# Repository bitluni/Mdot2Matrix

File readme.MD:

# M.2 LED Matrix

## Goal

This project is a showcase and starting point for M.2 PCIe hardware. The interface chip CH382 was used to inteface between the first PCIe lane and the CH32V208 MCU over UART.
Check out the [versionProject video](https://youtu.be/yxVQkL01FD4)

## State

RTS and DTR control flow signals are used to put the MCU into bootloader. !Caution This version is not working correctly as the signals are flipped on boot etc. Here is an updated [version](https://www.falstad.com/circuit/circuitjs.html?ctz=CQAgjCAMB0l3BWcAOaAmA7MgnGB-kA2MAFgwTREMJCQUloFMBaMMAKACcQS4QBmSCVoYag4QzDxIXETWaFhCUQKFQQaaewDmA5MLBj9AygxmaMGtAbTIrw5A2EAlACoBldhZ4k7C4SS+IKxglMIAhAAirs7sAO56wv4+fopQsvzGIZSZSWmSWt5o1sFBxUnYNMLRsc6JwWw5WaQS6rwC0PzqZtAIXpCWgXYtKSCVPCAAQgDy067mA1QIYmqEyxrrwgByzu6uOvXWDLkbNGYZFKV2tn5BBfAXlKHXyMO26lIPAC4Cl8xBJ3+dkkUF69EIkAhyDAlTQFAwlhgCEqhFwkLQhGscOIqhAABNGAAzACGAFcADZfdg-fiXZ71ekgpH4NBgZC2QykBGhUEIEjUQg4fS5MhdQT4olkynxBmBUYjGQJcrgd7K8TpBJDYJpZTyfLsAAy4DlQLG8ju4BAJPJAGdGB0ujIjSN6eNGZbrXaHekALIgDCaVTCUR2dWSaBrdh4+xBnh8dVPLbKUIZYxHBnYUzgaQyP1aka+SRy8ORzVBZJa-VluxpE5V+q14yNdI241JMolU1mK3E22MR7gMR-C2fODsVsu1Uld0MT39pXT1WvFXAgcwnJ0973McJXWxtYrCTsfiCpaHs8CE-dY+n-Ny-Mqc4JA+xgPHNQyVtv1+Bk-Aj29naBzfn+-q-sY5wAMZyLGe6gQYLCWGgsCQLgoSspg+jIBgeCgnAEAyLocGnnBEEahoy6msqXYyrSTxGAYZy0Vk-BNIx5EnCMnGZhxdI8dxpjsAAHhRlisMctLBIMKogAAqj6AASbBbOwABGGg4dqdi8AwgYyCJNyDkg-BXoY2kyfJSlgCp6mYBAUiDHwMJIDIAD2YwgP+JBSKY0B4JiLkoXA2CiMscLqJQ2ACFMszzOw7lSJ5bQ+bQeHwCFB7hbp2bRTsezxf6SVOClgUERohVdDUBVdF5JWgmVOTRW4nhAA)

In general the interface chip draws 170mA which puts the little LDO at it's limit. The thermals are terrible. Would not recomment to use this setup for a commercial project without a severe refinement.

## Tools

The firmware can be uploaded via the [wch web isp](https://github.com/basilhussain/wch-web-isp)

The code is written with the [MounRiver Studio](http://www.mounriver.com/download)

Node.js is required to run the websocket server

## Vibe coding

The majority of the web tool and the server are generated with ChatGPT which was trained on dacades of mine and your public code.

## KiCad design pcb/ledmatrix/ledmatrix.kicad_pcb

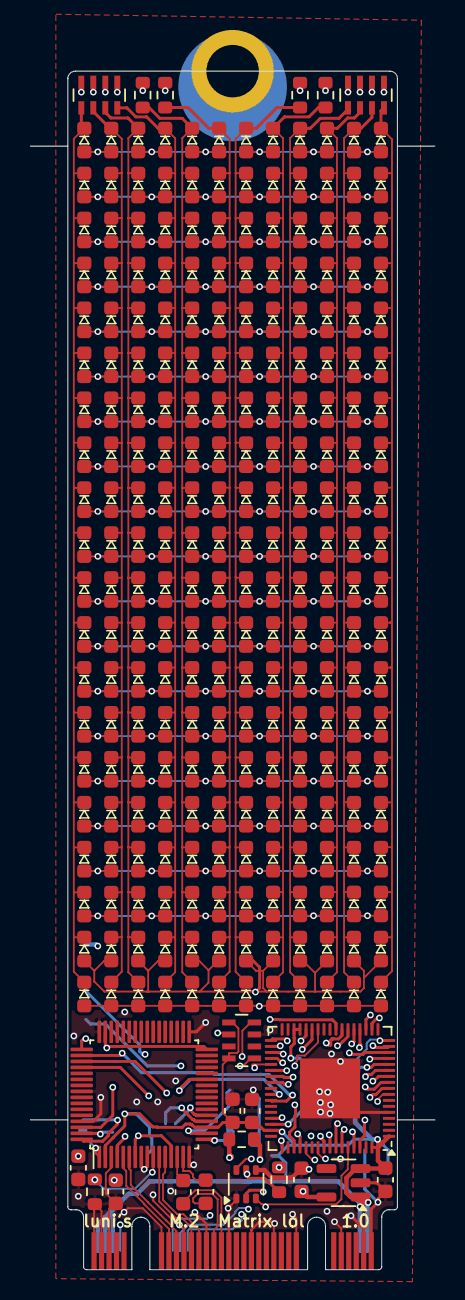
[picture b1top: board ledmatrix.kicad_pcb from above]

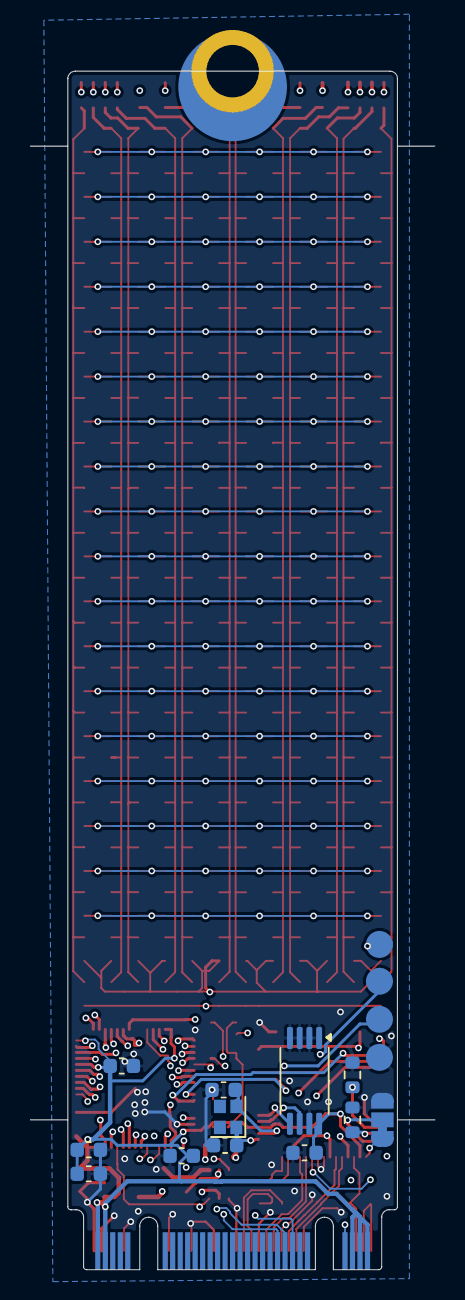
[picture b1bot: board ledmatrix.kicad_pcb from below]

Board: 4 copper layers, 27.0 x 80.0 mm, 276 parts (13 on the bottom side), 77 nets.

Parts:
C1, C2, C3, C10, C12, C15, C21, C22, C23, C24, C25: 100n; C_0603_1608Metric
C8, C11: 10u; C_0603_1608Metric
C16, C17: 27p; C_0603_1608Metric
D121, D122, D123, D124, D125, D126, D127, D128, D129, D130, D131, D132, D133, D134, D135, D136, D137, D138, D139, D140, D141, D142, D143, D144, D145, D146, D147, D148, D149, D150, D151, D152, D153, D154, D155, D156, D157, D158, D159, D160, D161, D162, D163, D164, D165, D166, D167, D168, D169, D170, D171, D172, D173, D174, D175, D176, D177, D178, D179, D180, D181, D182, D183, D184, D185, D186, D187, D188, D189, D190, D191, D192, D193, D194, D195, D196, D197, D198, D199, D200, D201, D202, D203, D204, D205, D206, D207, D208, D209, D210, D211, D212, D213, D214, D215, D216, D217, D218, D219, D220, D221, D222, D223, D224, D225, D226, D227, D228, D229, D230, D231, D232, D233, D234, D235, D236, D237, D238, D239, D240, D241, D242, D243, D244, D245, D246, D247, D248, D249, D250, D251, D252, D253, D254, D255, D256, D257, D258, D259, D260, D261, D262, D263, D264, D265, D266, D267, D268, D269, D270, D271, D272, D273, D274, D275, D276, D277, D278, D279, D280, D281, D282, D283, D284, D285, D286, D287, D288, D289, D290, D291, D292, D293, D294, D295, D296, D297, D298, D299, D300, D301, D302, D303, D304, D305, D306, D307, D308, D309, D310, D311, D312, D313, D314, D315, D316, D317, D318, D319, D320, D321, D322, D323, D324, D325, D326, D327, D328, D329, D330, D331, D332, D333, D334, D335, D336, D337, D338, D339, D340, D341, D342, D343, D344, D345, D346, D347, D348, D349, D350, D351, D352, D353, D354, D355, D356, D357, D358, D359, D360: LEDdiag0603; LED_0603
JP2: Jumper_3_Bridged12; SolderJumper-3_P1.3mm_Bridged12_RoundedPad1.0x1.5mm
Q1: UMH3N; SOT-363_SC-70-6
R8, R13, R14, R15, R16: 1k; R_0603_1608Metric
R9, R10, R11: 0; R_0603_1608Metric
R12: 12k; R_0603_1608Metric
RN5, RN6: 1k; R_Array_Concave_4x0603
RN8: 10k; R_Array_Concave_4x0603
TP1: TestPoint; Testpoint4
U1: CH382; LQFP-64_7x7mm_P0.4mm
U2: M.2-B+M-KEY-PCIe; M.2-B+M-KEY 2280
U4: M24C02-FDW; TSSOP-8_4.4x3mm_P0.65mm
U5: QFN-68-1EP_8x8mm_P0.4mm_EP4x4mm
U6: AP2112K-1.8; SOT-23-5
Y1: 22.1184MHz; Crystal_SMD_2016-4Pin_2.0x1.6mm

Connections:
1V8: C10.2, C11.2, R9.1, U1.4 (VCC18), U1.32 (VCC18), U1.47 (VCC18), U6.5 (VOUT)
1V8A: C12.2, R9.2, U1.7 (VCC18A), U1.13 (VCC18A)
/BOOT1: R8.2, U5.28 (PB2/BOOT1)
/CKSEL: JP2.2 (C), U1.64 (CKSEL)
/CLKREQ#: RN8.2 (R2.1), U2.P$52 (CLKREQ#)
/CLK_32k: U2.P$68 (SUSCLK(32kHz)), U5.58 (PB3)
/DTR: Q1.2 (B1), U1.52 (DTR0)
/PECK+: U1.5 (PECK+), U2.P$55 (REFCLK+)
/PECK-: U1.6 (PECK-), U2.P$53 (REFCLK-)
/PER+: U1.11 (PER+), U2.P$49 (PER0+)
/PER-: U1.12 (PER-), U2.P$47 (PER0-)
/PET+: C2.2, U1.15 (PET+)
/PET-: C1.2, U1.14 (PET-)
/RST#: JP2.1 (A), U1.1 (PERST#), U2.P$50 (PERST#)
/RST_CH32#: Q1.6 (C1), RN8.8 (R1.2), U5.8 (NRST)
/RTS: Q1.5 (B2), R8.1, U1.51 (RTS0)
/RX: U1.27 (RXD0), U5.44 (PA9)
/TX: U1.50 (TXD0), U5.45 (PA10)
/WAKE#: U2.P$54 (PEWAKE#), U5.56 (PC12)
BOOT0: Q1.3 (C2), RN8.5 (R4.2), U5.63 (BOOT0)
GND: C3.1, C8.1, C10.1, C11.1, C12.1, C15.1, C16.2, C17.2, C21.2, C22.2, C23.2, C24.2, C25.2, JP2.3 (B), Q1.1 (E1), Q1.4 (E2), R10.2, R11.2, R12.2, RN8.7 (R2.2), TP1.1, U1.3 (GND), U1.8 (GND), U1.9 (GND), U1.16 (GND), U1.33 (GND), U1.48 (GND), U1.56 (GND), U1.61 (GND), U2.P$1 (CONFIG3/GND), U2.P$3 (GND), U2.P$9 (GND), U2.P$21 (CONFIG_0/GND), U2.P$27 (GND), U2.P$33 (GND), U2.P$39 (GND), U2.P$45 (GND), U2.P$51 (GND), U2.P$57 (GND), U2.P$71 (GND), U2.P$73 (GND), U2.P$75 (CONFIG_2/GND), U4.1 (E0), U4.2 (E1), U4.3 (E2), U4.4 (VSS), U4.7 (~WC), U5.5 (VSSA), U5.49 (VSS_2), U5.69 (VSS), U6.2 (GND)
unnamed: D121.1 (K), D133.1 (K), D145.1 (K), D157.1 (K), D169.1 (K), D181.1 (K), D193.1 (K), D205.1 (K), D217.1 (K), D229.1 (K), D241.1 (K), D253.1 (K), D265.1 (K), D277.1 (K), D289.1 (K), D301.1 (K), D313.1 (K), D325.1 (K), D337.1 (K), D349.1 (K), RN5.4 (R4.1)
unnamed: D122.1 (K), D134.1 (K), D146.1 (K), D158.1 (K), D170.1 (K), D182.1 (K), D194.1 (K), D206.1 (K), D218.1 (K), D230.1 (K), D242.1 (K), D254.1 (K), D266.1 (K), D278.1 (K), D290.1 (K), D302.1 (K), D314.1 (K), D326.1 (K), D338.1 (K), D350.1 (K), RN5.3 (R3.1)
unnamed: D123.1 (K), D135.1 (K), D147.1 (K), D159.1 (K), D171.1 (K), D183.1 (K), D195.1 (K), D207.1 (K), D219.1 (K), D231.1 (K), D243.1 (K), D255.1 (K), D267.1 (K), D279.1 (K), D291.1 (K), D303.1 (K), D315.1 (K), D327.1 (K), D339.1 (K), D351.1 (K), RN5.2 (R2.1)
unnamed: D124.1 (K), D136.1 (K), D148.1 (K), D160.1 (K), D172.1 (K), D184.1 (K), D196.1 (K), D208.1 (K), D220.1 (K), D232.1 (K), D244.1 (K), D256.1 (K), D268.1 (K), D280.1 (K), D292.1 (K), D304.1 (K), D316.1 (K), D328.1 (K), D340.1 (K), D352.1 (K), RN5.1 (R1.1)
unnamed: D125.1 (K), D137.1 (K), D149.1 (K), D161.1 (K), D173.1 (K), D185.1 (K), D197.1 (K), D209.1 (K), D221.1 (K), D233.1 (K), D245.1 (K), D257.1 (K), D269.1 (K), D281.1 (K), D293.1 (K), D305.1 (K), D317.1 (K), D329.1 (K), D341.1 (K), D353.1 (K), R13.1
unnamed: D126.1 (K), D138.1 (K), D150.1 (K), D162.1 (K), D174.1 (K), D186.1 (K), D198.1 (K), D210.1 (K), D222.1 (K), D234.1 (K), D246.1 (K), D258.1 (K), D270.1 (K), D282.1 (K), D294.1 (K), D306.1 (K), D318.1 (K), D330.1 (K), D342.1 (K), D354.1 (K), R14.1
unnamed: D127.1 (K), D139.1 (K), D151.1 (K), D163.1 (K), D175.1 (K), D187.1 (K), D199.1 (K), D211.1 (K), D223.1 (K), D235.1 (K), D247.1 (K), D259.1 (K), D271.1 (K), D283.1 (K), D295.1 (K), D307.1 (K), D319.1 (K), D331.1 (K), D343.1 (K), D355.1 (K), R15.1
unnamed: D128.1 (K), D140.1 (K), D152.1 (K), D164.1 (K), D176.1 (K), D188.1 (K), D200.1 (K), D212.1 (K), D224.1 (K), D236.1 (K), D248.1 (K), D260.1 (K), D272.1 (K), D284.1 (K), D296.1 (K), D308.1 (K), D320.1 (K), D332.1 (K), D344.1 (K), D356.1 (K), R16.1
unnamed: D129.1 (K), D141.1 (K), D153.1 (K), D165.1 (K), D177.1 (K), D189.1 (K), D201.1 (K), D213.1 (K), D225.1 (K), D237.1 (K), D249.1 (K), D261.1 (K), D273.1 (K), D285.1 (K), D297.1 (K), D309.1 (K), D321.1 (K), D333.1 (K), D345.1 (K), D357.1 (K), RN6.4 (R4.1)
unnamed: D130.1 (K), D142.1 (K), D154.1 (K), D166.1 (K), D178.1 (K), D190.1 (K), D202.1 (K), D214.1 (K), D226.1 (K), D238.1 (K), D250.1 (K), D262.1 (K), D274.1 (K), D286.1 (K), D298.1 (K), D310.1 (K), D322.1 (K), D334.1 (K), D346.1 (K), D358.1 (K), RN6.3 (R3.1)
unnamed: D131.1 (K), D143.1 (K), D155.1 (K), D167.1 (K), D179.1 (K), D191.1 (K), D203.1 (K), D215.1 (K), D227.1 (K), D239.1 (K), D251.1 (K), D263.1 (K), D275.1 (K), D287.1 (K), D299.1 (K), D311.1 (K), D323.1 (K), D335.1 (K), D347.1 (K), D359.1 (K), RN6.2 (R2.1)
unnamed: D132.1 (K), D144.1 (K), D156.1 (K), D168.1 (K), D180.1 (K), D192.1 (K), D204.1 (K), D216.1 (K), D228.1 (K), D240.1 (K), D252.1 (K), D264.1 (K), D276.1 (K), D288.1 (K), D300.1 (K), D312.1 (K), D324.1 (K), D336.1 (K), D348.1 (K), D360.1 (K), RN6.1 (R1.1)
unnamed: R11.1, U1.62 (MDPRT#)
unnamed: R10.1, U1.63 (MDSEL)
unnamed: R12.1, U1.10 (RREF)
unnamed: U1.20 (SCL), U4.6 (SCL)
unnamed: U1.21 (SDA), U4.5 (SDA)
unnamed: C16.1, U1.18 (XI), Y1.2
unnamed: C17.1, U1.17 (XO), Y1.1
unnamed: C2.1, U2.P$43 (PET0+)
unnamed: C1.1, U2.P$41 (PET0-)
PA0: D121.2 (A), D122.2 (A), D123.2 (A), D124.2 (A), D125.2 (A), D126.2 (A), D127.2 (A), D128.2 (A), D129.2 (A), D130.2 (A), D131.2 (A), D132.2 (A), U5.14 (PA0/WKUP/ADC0)
PA1: D133.2 (A), D134.2 (A), D135.2 (A), D136.2 (A), D137.2 (A), D138.2 (A), D139.2 (A), D140.2 (A), D141.2 (A), D142.2 (A), D143.2 (A), D144.2 (A), U5.15 (PA1/ADC1)
PA2: D145.2 (A), D146.2 (A), D147.2 (A), D148.2 (A), D149.2 (A), D150.2 (A), D151.2 (A), D152.2 (A), D153.2 (A), D154.2 (A), D155.2 (A), D156.2 (A), U5.16 (PA2/ADC2)
PA3: D157.2 (A), D158.2 (A), D159.2 (A), D160.2 (A), D161.2 (A), D162.2 (A), D163.2 (A), D164.2 (A), D165.2 (A), D166.2 (A), D167.2 (A), D168.2 (A), U5.19 (PA3/ADC3)
PA4: D169.2 (A), D170.2 (A), D171.2 (A), D172.2 (A), D173.2 (A), D174.2 (A), D175.2 (A), D176.2 (A), D177.2 (A), D178.2 (A), D179.2 (A), D180.2 (A), U5.20 (PA4/ADC4)
PA5: D181.2 (A), D182.2 (A), D183.2 (A), D184.2 (A), D185.2 (A), D186.2 (A), D187.2 (A), D188.2 (A), D189.2 (A), D190.2 (A), D191.2 (A), D192.2 (A), U5.21 (PA5/ADC5)
PA6: D193.2 (A), D194.2 (A), D195.2 (A), D196.2 (A), D197.2 (A), D198.2 (A), D199.2 (A), D200.2 (A), D201.2 (A), D202.2 (A), D203.2 (A), D204.2 (A), U5.22 (PA6/ADC6)
PA7: D205.2 (A), D206.2 (A), D207.2 (A), D208.2 (A), D209.2 (A), D210.2 (A), D211.2 (A), D212.2 (A), D213.2 (A), D214.2 (A), D215.2 (A), D216.2 (A), U5.23 (PA7/ADC7)
PB4: D217.2 (A), D218.2 (A), D219.2 (A), D220.2 (A), D221.2 (A), D222.2 (A), D223.2 (A), D224.2 (A), D225.2 (A), D226.2 (A), D227.2 (A), D228.2 (A), U5.59 (PB4)
PB5: D229.2 (A), D230.2 (A), D231.2 (A), D232.2 (A), D233.2 (A), D234.2 (A), D235.2 (A), D236.2 (A), D237.2 (A), D238.2 (A), D239.2 (A), D240.2 (A), U5.60 (PB5)
PB6: D241.2 (A), D242.2 (A), D243.2 (A), D244.2 (A), D245.2 (A), D246.2 (A), D247.2 (A), D248.2 (A), D249.2 (A), D250.2 (A), D251.2 (A), D252.2 (A), U5.61 (PB6/USB2DM)
PB7: D253.2 (A), D254.2 (A), D255.2 (A), D256.2 (A), D257.2 (A), D258.2 (A), D259.2 (A), D260.2 (A), D261.2 (A), D262.2 (A), D263.2 (A), D264.2 (A), U5.62 (PB7/USB2DP)
PB8: D265.2 (A), D266.2 (A), D267.2 (A), D268.2 (A), D269.2 (A), D270.2 (A), D271.2 (A), D272.2 (A), D273.2 (A), D274.2 (A), D275.2 (A), D276.2 (A), U5.64 (PB8)
PB9: D277.2 (A), D278.2 (A), D279.2 (A), D280.2 (A), D281.2 (A), D282.2 (A), D283.2 (A), D284.2 (A), D285.2 (A), D286.2 (A), D287.2 (A), D288.2 (A), U5.65 (PB9)
PB10: D289.2 (A), D290.2 (A), D291.2 (A), D292.2 (A), D293.2 (A), D294.2 (A), D295.2 (A), D296.2 (A), D297.2 (A), D298.2 (A), D299.2 (A), D300.2 (A), U5.29 (PB10)
PB11: D301.2 (A), D302.2 (A), D303.2 (A), D304.2 (A), D305.2 (A), D306.2 (A), D307.2 (A), D308.2 (A), D309.2 (A), D310.2 (A), D311.2 (A), D312.2 (A), U5.30 (PB11)
PB12: D313.2 (A), D314.2 (A), D315.2 (A), D316.2 (A), D317.2 (A), D318.2 (A), D319.2 (A), D320.2 (A), D321.2 (A), D322.2 (A), D323.2 (A), D324.2 (A), U5.35 (PB12)
PB13: D325.2 (A), D326.2 (A), D327.2 (A), D328.2 (A), D329.2 (A), D330.2 (A), D331.2 (A), D332.2 (A), D333.2 (A), D334.2 (A), D335.2 (A), D336.2 (A), U5.36 (PB13)
PB14: D337.2 (A), D338.2 (A), D339.2 (A), D340.2 (A), D341.2 (A), D342.2 (A), D343.2 (A), D344.2 (A), D345.2 (A), D346.2 (A), D347.2 (A), D348.2 (A), U5.37 (PB14)
PB15: D349.2 (A), D350.2 (A), D351.2 (A), D352.2 (A), D353.2 (A), D354.2 (A), D355.2 (A), D356.2 (A), D357.2 (A), D358.2 (A), D359.2 (A), D360.2 (A), U5.38 (PB15)
PC0: RN5.5 (R4.2), U5.9 (PC0/ADC10)
PC1: RN5.6 (R3.2), U5.10 (PC1/ADC11)
PC2: RN5.7 (R2.2), U5.11 (PC2/ADC12)
PC3: RN5.8 (R1.2), U5.12 (PC3/ADC13)
PC4: R13.2, U5.24 (PC4/ADC14)
PC5: R14.2, U5.25 (PC5/ADC15)
PC6: R15.2, U5.39 (PC6/RXP)
PC7: R16.2, U5.40 (PC7/RXN)
PC8: RN6.5 (R4.2), U5.41 (PC8/TXP)
PC9: RN6.6 (R3.2), U5.42 (PC9/TXN)
PC10: RN6.7 (R2.2), U5.54 (PC10)
PC11: RN6.8 (R1.2), U5.55 (PC11)
SWDCLK: TP1.2, U5.52 (PA14/SWCLK)
SWDIO: TP1.3, U5.48 (PA13/SWDIO)
VCC: C3.2, C8.2, C15.2, C21.1, C22.1, C23.1, C24.1, C25.1, RN8.1 (R1.1), RN8.4 (R4.1), TP1.4, U1.2 (VCC33), U1.19 (VCC33), U1.49 (VCC33), U2.P$2 (3V3), U2.P$4 (3V3), U2.P$70 (3V3), U2.P$72 (3V3), U2.P$74 (3V3), U4.8 (VCC), U5.1 (VBAT), U5.13 (VDDA), U5.17 (VIO_4), U5.31 (VIO_1), U5.32 (VDD_1), U5.50 (VINTA), U5.67 (VIO_3), U5.68 (VDD_3), U6.1 (VIN), U6.3 (EN)

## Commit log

2025-05-03 Create LICENSE
2025-05-08 ooops wrong version
